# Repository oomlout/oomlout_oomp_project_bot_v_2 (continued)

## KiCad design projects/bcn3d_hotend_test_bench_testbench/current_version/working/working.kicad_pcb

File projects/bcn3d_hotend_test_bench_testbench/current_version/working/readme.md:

# hotend_test_bench
 
## summary 
* id: bcn3d_hotend_test_bench_testbench
* user: bcn3d
* name: hotend_test_bench
* board: testbench
* repo: https://github.com/BCN3D/Hotend-Test-Bench

* src_file_repo_sch: 
* src_file_repo_sch_link: https://github.com/BCN3D/Hotend-Test-Bench/tree/master/
* full details link: https://github.com/oomlout/oomlout_oomp_project_bot_v_2/tree/main/projects/bcn3d_hotend_test_bench_testbench/current_version/working  

## schematic  
  
[schematic (pdf)](working_schematic.pdf) 

## pcb  

[board (pdf)](working.pdf)  

## working_bom
| Id | Designator | Footprint | Quantity | Designation | Supplier and ref |  | None | 
| --- | --- | --- | --- | --- | --- | --- | --- | 
| 1 | R21,R13,R5,R17,R1,R9,R25 | R0805 | 7 | 5k6 |  |  | [''] | 
| 2 | C3,C12,C1,C13,C18,C15,C17,C11,C6,C19,C10,C9,C4,C16,C5,C2 | C0805K | 16 | 100n |  |  | [''] | 
| 3 | F1 | PTC-1206-WIDE | 1 | PTCSMD-W |  |  | [''] | 
| 4 | C7,C8 | C0805K | 2 | 22p |  |  | [''] | 
| 5 | R11,R15,R7,R23,R26,R3,R19 | R0805 | 7 | 10k |  |  | [''] | 
| 6 | R14,R18,R10,R2,R22,R6 | R0805 | 6 | 100 |  |  | [''] | 
| 7 | D5,D1,D7,D3,D4,D6,D2 | SMA-DIODE | 7 | MBRA140 |  |  | [''] | 
| 8 | R20,R8,R24,R12,R4,R16 | R0805 | 6 | 4k7 |  |  | [''] | 
| 9 | Q3,Q2,Q6,Q4,Q1,Q5 | SOIC8 | 6 | MOSFET-N |  |  | [''] | 
| 10 | C14 | C0805K | 1 | 330n |  |  | [''] | 
| 11 | LED3,LED1,LED5,LED4,LED6,LED2,LED16,LED13,LED14,LED18,+5V0,LED15,LED10,LED8,LED11,LED17,LED9,LED12,LED7,+24V0 | CHIP-LED0805 | 20 |  |  |  | [''] | 
| 12 | PC1 | MOLEX_MINIFIT-JR | 1 | POWER INPUT |  |  | [''] | 
| 13 | HOTEND5,HOTEND6,HOTEND1,HOTEND3,HOTEND2,HOTEND4 | 1X04 | 6 |  |  |  | [''] | 
| 14 | @HOLE0,@HOLE1 |  | 2 |  |  |  | [''] | 
| 15 | U1 | TQFP32-08 | 1 | ATMEGA328P_TQFP |  |  | [''] | 
| 16 | IC2,IC1 | SO16 | 2 | 74LS595D |  |  | [''] | 
| 17 | RESET0 | EVQ-Q2 | 1 | SPST_TACT-EVQQ2 |  |  | [''] | 
| 18 | U$3 | OSHW-LOGO-L | 1 |  |  |  | [''] | 
| 19 | ICSP0 | 2X3 | 1 | AVR_SPI_PRG_6PTH |  |  | [''] | 
| 20 | Y1 | HC49US | 1 | 16MHz |  |  | [''] | 
| 21 | U2 | TO-252 | 1 | KA7805ERTF |  |  | [''] | 
| 22 | JP8 | FTDI_BASIC | 1 | FTDI_BASICPTH |  |  | [''] | 
| 23 | RN2,RN3,RN1 | CTS742C083 | 3 | CTS742C083 |  |  | [''] | 
| 24 | R27 | R0805 | 1 | 1k |  |  | [''] | 
| 25 | U$2 | BCN3D_LOGO | 1 |  |  |  | [''] | 
| 26 | U$1 | FCIM_LOGO | 1 |  |  |  | [''] | 

## bom_schematic
| Ref | Qnty | Value | Cmp name | Footprint | Description | Vendor | DNP | 
| --- | --- | --- | --- | --- | --- | --- | --- | 
| +5V0 | 1 | LEDCHIP-LED0805 | LEDCHIP-LED0805 | working:CHIP-LED0805 |  |  |  | 
| +24V0 | 1 | LEDCHIP-LED0805 | LEDCHIP-LED0805 | working:CHIP-LED0805 |  |  |  | 
| C1, C2, C3, C4, C5, C6, C9, C10, C11, C12, C13, C15, C16, C17, C18, C19 | 16 | 100n | C-USC0805K | working:C0805K |  |  |  | 
| C7, C8 | 2 | 22p | C-USC0805K | working:C0805K |  |  |  | 
| C14 | 1 | 330n | C-USC0805K | working:C0805K |  |  |  | 
| D1, D2, D3, D4, D5, D6, D7 | 7 | MBRA140 | MBRA140 | working:SMA-DIODE |  |  |  | 
| F1 | 1 | PTCSMD-W | PTCSMD-W | working:PTC-1206-WIDE |  |  |  | 
| HOTEND1, HOTEND2, HOTEND3, HOTEND4, HOTEND5, HOTEND6 | 6 | PINHD-1X4 | PINHD-1X4 | working:1X04 |  |  |  | 
| IC1, IC2 | 2 | 74595D | 74595D | working:SO16 |  |  |  | 
| ICSP0 | 1 | AVR_SPI_PRG_6PTH | AVR_SPI_PRG_6PTH | working:2X3 |  |  |  | 
| JP8 | 1 | FTDI_BASICPTH | FTDI_BASICPTH | working:FTDI_BASIC |  |  |  | 
| LED1, LED2, LED3, LED4, LED5, LED6, LED7, LED8, LED9, LED10, LED11, LED12, LED13, LED14, LED15, LED16, LED17, LED18 | 18 | LEDCHIP-LED0805 | LEDCHIP-LED0805 | working:CHIP-LED0805 |  |  |  | 
| PC1 | 1 | POWER_CONNECTOR_4WAY | POWER_CONNECTOR_4WAY | working:MOLEX_MINIFIT-JR |  |  |  | 
| Q1, Q2, Q3, Q4, Q5, Q6 | 6 | MOSFET-N | MarcEagleParts_MOSFET-N | working:SOIC8 |  |  |  | 
| R1, R5, R9, R13, R17, R21, R25 | 7 | 5k6 | R-US_R0805 | working:R0805 |  |  |  | 
| R2, R6, R10, R14, R18, R22 | 6 | 100 | R-US_R0805 | working:R0805 |  |  |  | 
| R3, R7, R11, R15, R19, R23, R26 | 7 | 10k | R-US_R0805 | working:R0805 |  |  |  | 
| R4, R8, R12, R16, R20, R24 | 6 | 4k7 | R-US_R0805 | working:R0805 |  |  |  | 
| R27 | 1 | 1k | R-US_R0805 | working:R0805 |  |  |  | 
| RESET0 | 1 | SPST_TACT-EVQQ2 | SPST_TACT-EVQQ2 | working:EVQ-Q2 |  |  |  | 
| RN1, RN2, RN3 | 3 | CTS742C083 | CTS742C083 | working:CTS742C083 |  |  |  | 
| U1 | 1 | ATMEGA328P_TQFP | ATMEGA328P_TQFP | working:TQFP32-08 |  |  |  | 
| U2 | 1 | KA7805ERTF | V_REG_78XX7812 | working:TO-252 |  |  |  | 
| Y1 | 1 | 16MHz | CRYSTALHC49US | working:HC49US |  |  |  |

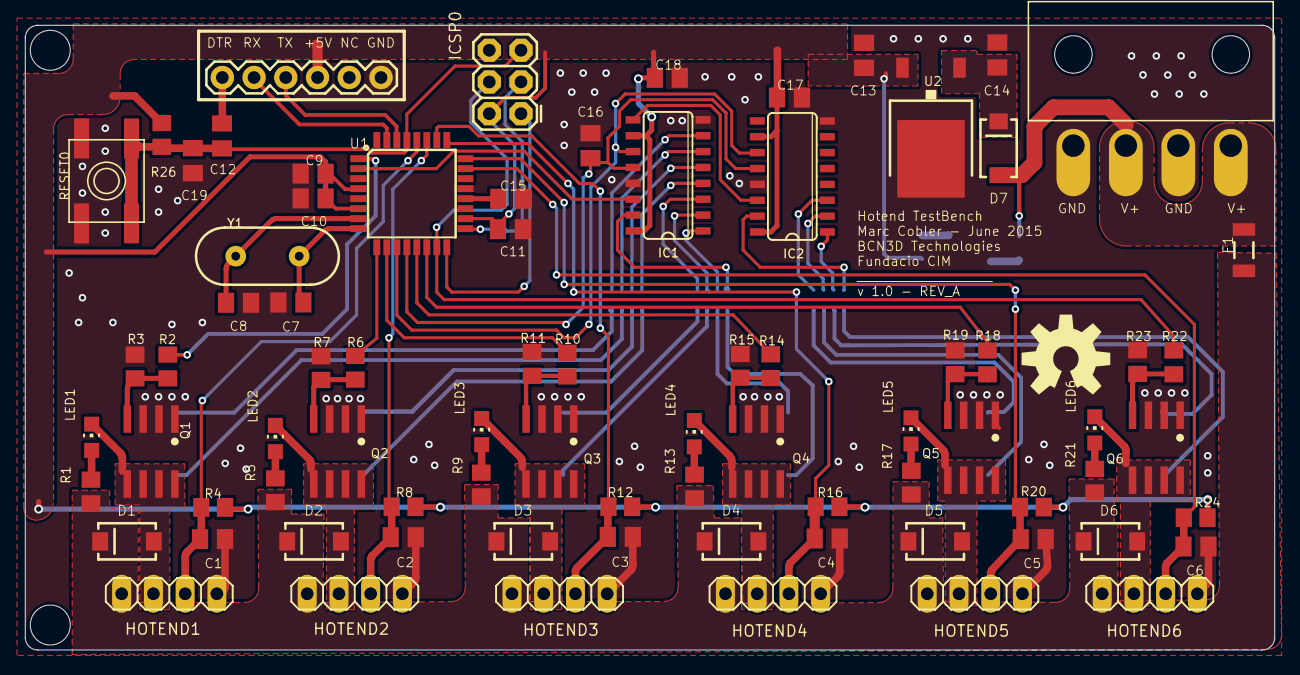
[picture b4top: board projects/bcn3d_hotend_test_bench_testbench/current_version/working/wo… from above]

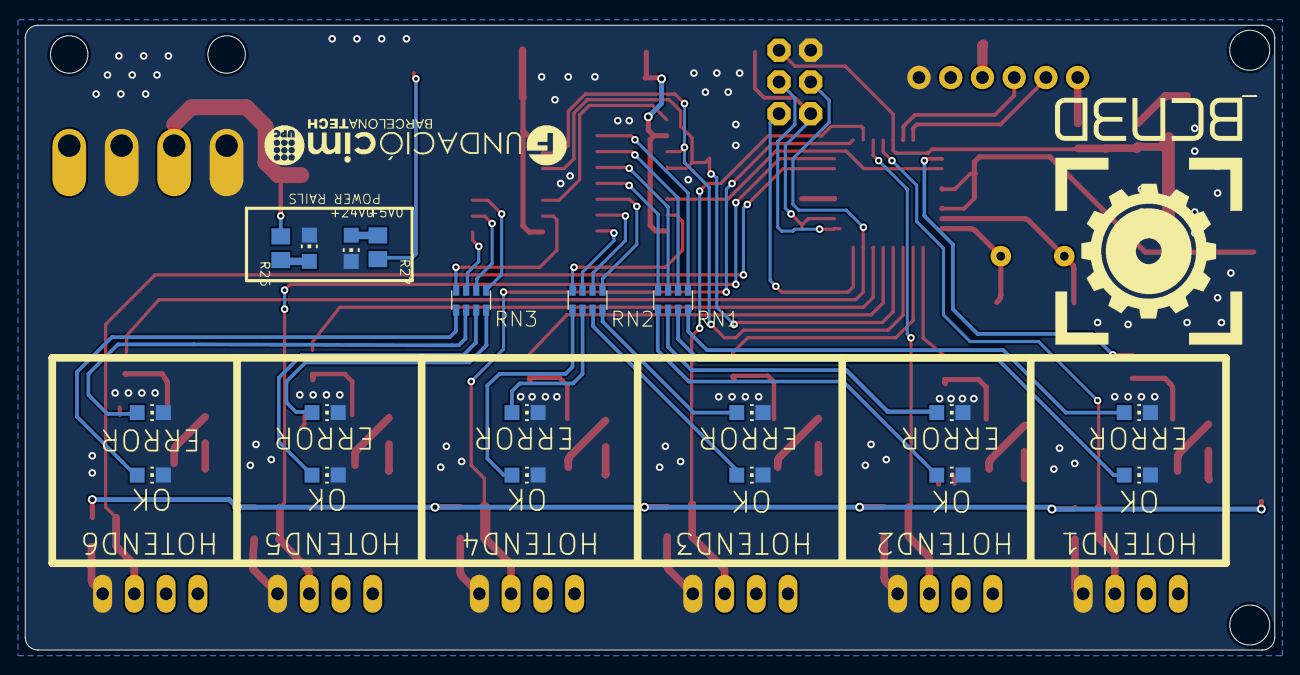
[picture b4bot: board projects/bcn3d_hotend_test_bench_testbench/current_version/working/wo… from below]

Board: 2 copper layers, 100.0 x 50.0 mm, 103 parts (21 on the bottom side), 74 nets.

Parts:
+5V0, +24V0: CHIP-LED0805
@HOLE0, @HOLE1: (no value)
C1, C2, C3, C4, C5, C6, C9, C10, C11, C12, C13, C15, C16, C17, C18, C19: 100n; C0805K
C7, C8: 22p; C0805K
C14: 330n; C0805K
D1, D2, D3, D4, D5, D6, D7: MBRA140; SMA-DIODE
F1: PTCSMD-W; PTC-1206-WIDE
HOTEND1, HOTEND2, HOTEND3, HOTEND4, HOTEND5, HOTEND6: 1X04
IC1, IC2: 74LS595D; SO16
ICSP0: AVR_SPI_PRG_6PTH; 2X3
JP8: FTDI_BASICPTH; FTDI_BASIC
LED1, LED2, LED3, LED4, LED5, LED6, LED7, LED8, LED9, LED10, LED11, LED12, LED13, LED14, LED15, LED16, LED17, LED18: CHIP-LED0805
PC1: POWER INPUT; MOLEX_MINIFIT-JR
Q1, Q2, Q3, Q4, Q5, Q6: MOSFET-N; SOIC8
R1, R5, R9, R13, R17, R21, R25: 5k6; R0805
R2, R6, R10, R14, R18, R22: 100; R0805
R3, R7, R11, R15, R19, R23, R26: 10k; R0805
R4, R8, R12, R16, R20, R24: 4k7; R0805
R27: 1k; R0805
RESET0: SPST_TACT-EVQQ2; EVQ-Q2
RN1, RN2, RN3: CTS742C083
U1: ATMEGA328P_TQFP; TQFP32-08
U2: KA7805ERTF; TO-252
U$1: FCIM_LOGO
U$2: BCN3D_LOGO
U$3: OSHW-LOGO-L
Y1: 16MHz; HC49US

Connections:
+5V: C9.1, C10.1, C11.1, C13.1, C17.1, C18.1, IC1.10, IC1.16, IC2.10, IC2.16, ICSP0.2, JP8.VCC, R4.1, R8.1, R12.1, R16.1, R20.1, R24.1, R26.1, R27.2, U1.4, U1.6, U1.18, U2.2
+24V: D7.A, F1.1, PC1.1, PC1.3, R25.2
+24VHE: D1.C, D2.C, D3.C, D4.C, D5.C, D6.C, F1.2, HOTEND1.1, HOTEND2.1, HOTEND3.1, HOTEND4.1, HOTEND5.1, HOTEND6.1, R1.2, R5.2, R9.2, R13.2, R17.2, R21.2
CLK: IC1.11, IC2.11, U1.11
DATA: IC1.14, U1.2
DTR: C12.2, JP8.DTR
GND: +5V0.C, +24V0.C, C1.2, C2.2, C3.2, C4.2, C5.2, C6.2, C7.2, C8.2, C9.2, C10.2, C11.2, C13.2, C14.2, C15.2, C16.2, C17.2, C18.2, C19.2, HOTEND1.4, HOTEND2.4, HOTEND3.4, HOTEND4.4, HOTEND5.4, HOTEND6.4, IC1.8, IC1.13, IC2.8, IC2.13, ICSP0.6, JP8.GND, LED7.C, LED8.C, LED9.C, LED10.C, LED11.C, LED12.C, LED13.C, LED14.C, LED15.C, LED16.C, LED17.C, LED18.C, PC1.2, PC1.4, Q1.1, Q1.2, Q1.3, Q2.1, Q2.2, Q2.3, Q3.1, Q3.2, Q3.3, Q4.1, Q4.2, Q4.3, Q5.1, Q5.2, Q5.3, Q6.1, Q6.2, Q6.3, R3.2, R7.2, R11.2, R15.2, R19.2, R23.2, RESET0.B, RESET0.B', U1.3, U1.5, U1.21, U2.3
H1: D1.A, HOTEND1.2, LED1.C, Q1.5, Q1.6, Q1.7, Q1.8
H2: D2.A, HOTEND2.2, LED2.C, Q2.5, Q2.6, Q2.7, Q2.8
H3: D3.A, HOTEND3.2, LED3.C, Q3.5, Q3.6, Q3.7, Q3.8
H4: D4.A, HOTEND4.2, LED4.C, Q4.5, Q4.6, Q4.7, Q4.8
H5: D5.A, HOTEND5.2, LED5.C, Q5.5, Q5.6, Q5.7, Q5.8
H6: D6.A, HOTEND6.2, LED6.C, Q6.5, Q6.6, Q6.7, Q6.8
LATCH: C16.1, IC1.12, IC2.12, U1.12
LED0: IC1.15, RN2.4
LED1: IC1.1, RN2.3
LED2: IC1.2, RN2.2
LED3: IC1.3, RN2.1
LED4: IC1.4, RN1.4
LED5: IC1.5, RN1.3
LED6: IC1.6, RN1.2
LED7: IC1.7, RN1.1
LED8: IC2.15, RN3.4
LED9: IC2.1, RN3.3
LED10: IC2.2, RN3.2
LED11: IC2.3, RN3.1
MISO: ICSP0.1, U1.16
unnamed: Q1.4, R2.1, R3.1
unnamed: +24V0.A, R25.1
unnamed: LED1.A, R1.1
unnamed: Q5.4, R18.1, R19.1
unnamed: C7.1, U1.8, Y1.1
unnamed: LED7.A, RN1.8
unnamed: Q2.4, R6.1, R7.1
unnamed: LED2.A, R5.1
unnamed: Q3.4, R10.1, R11.1
unnamed: LED3.A, R9.1
unnamed: Q4.4, R14.1, R15.1
unnamed: LED4.A, R13.1
unnamed: LED5.A, R17.1
unnamed: Q6.4, R22.1, R23.1
unnamed: LED6.A, R21.1
unnamed: C8.1, U1.7, Y1.2
unnamed: C15.1, U1.20
unnamed: C14.1, D7.C, U2.1
unnamed: LED8.A, RN1.7
unnamed: LED9.A, RN1.6
unnamed: LED10.A, RN1.5
unnamed: LED11.A, RN2.8
unnamed: LED12.A, RN2.7
unnamed: LED13.A, RN2.6
unnamed: LED14.A, RN2.5
unnamed: LED15.A, RN3.8
unnamed: LED16.A, RN3.7
unnamed: LED17.A, RN3.6
unnamed: LED18.A, RN3.5
unnamed: IC1.9, IC2.14
unnamed: +5V0.A, R27.1
PWM0: R2.2, U1.1
PWM1: R6.2, U1.9
PWM2: R10.2, U1.10
PWM3: R14.2, U1.13
PWM4: R18.2, U1.14
PWM5: ICSP0.4, R22.2, U1.15
RX: JP8.RXI, U1.31
SCK: ICSP0.3, U1.17
THERM0: C1.1, HOTEND1.3, R4.2, U1.28
THERM1: C2.1, HOTEND2.3, R8.2, U1.27
THERM2: C3.1, HOTEND3.3, R12.2, U1.26
THERM3: C4.1, HOTEND4.3, R16.2, U1.25
THERM4: C5.1, HOTEND5.3, R20.2, U1.24
THERM5: C6.1, HOTEND6.3, R24.2, U1.23
TX: JP8.TXO, U1.30
~RESET: C12.1, C19.1, ICSP0.5, R26.2, RESET0.A, RESET0.A', U1.29

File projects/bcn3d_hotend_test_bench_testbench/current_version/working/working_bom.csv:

"Id";"Designator";"Footprint";"Quantity";"Designation";"Supplier and ref";
1;"R21,R13,R5,R17,R1,R9,R25";"R0805";7;"5k6";;;
2;"C3,C12,C1,C13,C18,C15,C17,C11,C6,C19,C10,C9,C4,C16,C5,C2";"C0805K";16;"100n";;;
3;"F1";"PTC-1206-WIDE";1;"PTCSMD-W";;;
4;"C7,C8";"C0805K";2;"22p";;;
5;"R11,R15,R7,R23,R26,R3,R19";"R0805";7;"10k";;;
6;"R14,R18,R10,R2,R22,R6";"R0805";6;"100";;;
7;"D5,D1,D7,D3,D4,D6,D2";"SMA-DIODE";7;"MBRA140";;;
8;"R20,R8,R24,R12,R4,R16";"R0805";6;"4k7";;;
9;"Q3,Q2,Q6,Q4,Q1,Q5";"SOIC8";6;"MOSFET-N";;;
10;"C14";"C0805K";1;"330n";;;
11;"LED3,LED1,LED5,LED4,LED6,LED2,LED16,LED13,LED14,LED18,+5V0,LED15,LED10,LED8,LED11,LED17,LED9,LED12,LED7,+24V0";"CHIP-LED0805";20;"";;;
12;"PC1";"MOLEX_MINIFIT-JR";1;"POWER INPUT";;;
13;"HOTEND5,HOTEND6,HOTEND1,HOTEND3,HOTEND2,HOTEND4";"1X04";6;"";;;
14;"@HOLE0,@HOLE1";"";2;"";;;
15;"U1";"TQFP32-08";1;"ATMEGA328P_TQFP";;;
16;"IC2,IC1";"SO16";2;"74LS595D";;;
17;"RESET0";"EVQ-Q2";1;"SPST_TACT-EVQQ2";;;
18;"U$3";"OSHW-LOGO-L";1;"";;;
19;"ICSP0";"2X3";1;"AVR_SPI_PRG_6PTH";;;
20;"Y1";"HC49US";1;"16MHz";;;
21;"U2";"TO-252";1;"KA7805ERTF";;;
22;"JP8";"FTDI_BASIC";1;"FTDI_BASICPTH";;;
23;"RN2,RN3,RN1";"CTS742C083";3;"CTS742C083";;;
24;"R27";"R0805";1;"1k";;;
25;"U$2";"BCN3D_LOGO";1;"";;;
26;"U$1";"FCIM_LOGO";1;"";;;

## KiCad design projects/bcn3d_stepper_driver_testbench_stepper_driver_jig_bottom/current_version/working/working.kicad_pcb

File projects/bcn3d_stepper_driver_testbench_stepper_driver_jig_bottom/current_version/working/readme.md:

# stepper_driver_testbench
 
## summary 
* id: bcn3d_stepper_driver_testbench_stepper_driver_jig_bottom
* user: bcn3d
* name: stepper_driver_testbench
* board: stepper_driver_jig_bottom
* repo: https://github.com/BCN3D/Stepper-Driver-testbench

* src_file_repo_sch: 
* src_file_repo_sch_link: https://github.com/BCN3D/Stepper-Driver-testbench/tree/master/
* full details link: https://github.com/oomlout/oomlout_oomp_project_bot_v_2/tree/main/projects/bcn3d_stepper_driver_testbench_stepper_driver_jig_bottom/current_version/working  

## schematic  
  
[schematic (pdf)](working_schematic.pdf) 

## pcb  

[board (pdf)](working.pdf)  

## working_bom
| Id | Designator | Footprint | Quantity | Designation | Supplier and ref |  | None | 
| --- | --- | --- | --- | --- | --- | --- | --- | 
| 1 | R29,R30,R13,R12,R16,R1,R28,R4,R27,R18,R2,R14,R15,R3,R17,R11 | M0805 | 16 |  |  |  | [''] | 
| 2 | FTDI0 | FTDI_BASIC | 1 | FTDI_BASICPTH |  |  | [''] | 
| 3 | R7,R26,R8 | M0805 | 3 | 68.1K |  |  | [''] | 
| 4 | LED1 | CHIP-LED0805 | 1 |  |  |  | [''] | 
| 5 | @HOLE0,@HOLE1 |  | 2 |  |  |  | [''] | 
| 6 | U$11 | BCN3D_LOGO | 1 |  |  |  | [''] | 
| 7 | JP12,JP10,JP15,JP9,JP6,JP11,JP13,JP7,JP5,JP2,JP14,JP4,JP3,JP8 | POGOPIN | 14 |  |  |  | [''] | 
| 8 | U$3 | USB-B-PTH | 1 | USB+SHIELD |  |  | [''] | 
| 9 | JST0 | JST-PH-2-SMT-RA | 1 |  |  |  | [''] | 
| 10 | U$9,U$6,U$7,U$5,U$4,U$8 | STAND-OFF | 6 |  |  |  | [''] | 
| 11 | R20,R19 | M0805 | 2 | 10M |  |  | [''] | 
| 12 | RESET0 | EVQ-Q2 | 1 | SPST_TACT-EVQQ2 |  |  | [''] | 
| 13 | U$10 | FCIM_LOGO | 1 |  |  |  | [''] | 
| 14 | U$1,U$2 | CAPSENSE_PAD | 2 | CAPSENSE_PAD |  |  | [''] | 
| 15 | Q2 | SOT23-3 | 1 | MMBT2222A |  |  | [''] | 
| 16 | LOW0,HIGH0,OK0 | CHIPLED_1206 | 3 |  |  |  | [''] | 
| 17 | R10,R31,R5,R6 | M0805 | 4 | 1K |  |  | [''] | 
| 18 | R24,R25 | M0805 | 2 | 5.6K |  |  | [''] | 
| 19 | C5,C13,C9,C8,C6,C1,C7,C12 | C0805 | 8 | 100n |  |  | [''] | 
| 20 | LED4,LED5 | CHIPLED_0805 | 2 |  |  |  | [''] | 
| 21 | U1 | TO-252 | 1 | +5V |  |  | [''] | 
| 22 | C4 | UD-8X10_NICHICON | 1 | 100uF |  |  | [''] | 
| 23 | R22 | M0805 | 1 | 100 |  |  | [''] | 
| 24 | S2,S1 | SWITCH-SPDT_KIT | 2 |  |  |  | [''] | 
| 25 | SCREW0 | 1X01 | 1 |  |  |  | [''] | 
| 26 | R21,R23,R9 | M0805 | 3 | 10K |  |  | [''] | 
| 27 | IC2 | SO14 | 1 | LM339D |  |  | [''] | 
| 28 | Q3 | TO220V | 1 | MOSFET-PCHANNELFQP27P06 |  |  | [''] | 
| 29 | JP1 | POWER_JACK_PTH | 1 | POWER_JACKPTH |  |  | [''] | 
| 30 | MOTOR0 | 1X04 | 1 |  |  |  | [''] | 
| 31 | U3 | TQFP32-08 | 1 | ATMEGA328P |  |  | [''] | 
| 32 | C2 | C0805 | 1 | 1uF |  |  | [''] | 
| 33 | C10,C11 | C0805 | 2 | 22p |  |  | [''] | 
| 34 | Y1 | HC49US | 1 |  |  |  | [''] | 
| 35 | SH1 | SHORT_TOP-50 | 1 | SHORTT5 |  |  | [''] | 
| 36 | PORTC0 | 1X08 | 1 |  |  |  | [''] | 
| 37 | U2 | SO16 | 1 | 74HC4052 |  |  | [''] | 
| 38 | C3 | C0805 | 1 | 0.33uF |  |  | [''] | 
| 39 | ICSP0 | 2X3 | 1 | AVR_SPI_PRG_6PTH |  |  | [''] | 

## bom_schematic
| Ref | Qnty | Value | Cmp name | Footprint | Description | Vendor | DNP | 
| --- | --- | --- | --- | --- | --- | --- | --- | 
| C1, C5, C6, C7, C8, C9, C12, C13 | 8 | 100n | C-USC0805 | working:C0805 |  |  |  | 
| C2 | 1 | 1uF | C-USC0805 | working:C0805 |  |  |  | 
| C3 | 1 | 0.33uF | C-USC0805 | working:C0805 |  |  |  | 
| C4 | 1 | 100uF | CPOL-USUD-8X10 | working:UD-8X10_NICHICON |  |  |  | 
| C10, C11 | 2 | 22p | C-USC0805 | working:C0805 |  |  |  | 
| FTDI0 | 1 | FTDI_BASICPTH | FTDI_BASICPTH | working:FTDI_BASIC |  |  |  | 
| HIGH0 | 1 | LEDCHIPLED_1206 | LEDCHIPLED_1206 | working:CHIPLED_1206 |  |  |  | 
| IC2 | 1 | LM339D | LM339D | working:SO14 |  |  |  | 
| ICSP0 | 1 | AVR_SPI_PRG_6PTH | AVR_SPI_PRG_6PTH | working:2X3 |  |  |  | 
| JP1 | 1 | POWER_JACKPTH | POWER_JACKPTH | working:POWER_JACK_PTH |  |  |  | 
| JP2, JP3, JP4, JP5, JP6, JP7, JP8, JP9, JP10, JP11, JP12, JP13, JP14, JP15 | 14 | PINHD-1X1 | MarcEagleParts_PINHD-1X1 | working:POGOPIN |  |  |  | 
| JST0 | 1 | JST_2PIN-SMT-RA | JST_2PIN-SMT-RA | working:JST-PH-2-SMT-RA |  |  |  | 
| LED1 | 1 | LEDCHIP-LED0805 | LEDCHIP-LED0805 | working:CHIP-LED0805 |  |  |  | 
| LED4, LED5 | 2 | LEDCHIPLED_0805 | LEDCHIPLED_0805 | working:CHIPLED_0805 |  |  |  | 
| LOW0 | 1 | LEDCHIPLED_1206 | LEDCHIPLED_1206 | working:CHIPLED_1206 |  |  |  | 
| MOTOR0 | 1 | PINHD-1X4 | PINHD-1X4 | working:1X04 |  |  |  | 
| OK0 | 1 | LEDCHIPLED_1206 | LEDCHIPLED_1206 | working:CHIPLED_1206 |  |  |  | 
| PORTC0 | 1 | PINHD-1X8 | PINHD-1X8 | working:1X08 |  |  |  | 
| Q2 | 1 | MMBT2222A | TRANSISTOR_NPNMMBT2222A | working:SOT23-3 |  |  |  | 
| Q3 | 1 | MOSFET-PCHANNELFQP27P06 | MOSFET-PCHANNELFQP27P06 | working:TO220V |  |  |  | 
| R1, R2, R3, R4, R11, R12, R13, R14, R15, R16, R17, R18, R27, R28, R29, R30 | 16 | R-US_M0805 | R-US_M0805 | working:M0805 |  |  |  | 
| R5, R6, R10, R31 | 4 | 1K | R-US_M0805 | working:M0805 |  |  |  | 
| R7, R8, R26 | 3 | 68.1K | R-US_M0805 | working:M0805 |  |  |  | 
| R9, R21, R23 | 3 | 10K | R-US_M0805 | working:M0805 |  |  |  | 
| R19, R20 | 2 | 10M | R-US_M0805 | working:M0805 |  |  |  | 
| R22 | 1 | 100 | R-US_M0805 | working:M0805 |  |  |  | 
| R24, R25 | 2 | 5.6K | R-US_M0805 | working:M0805 |  |  |  | 
| RESET0 | 1 | SPST_TACT-EVQQ2 | SPST_TACT-EVQQ2 | working:EVQ-Q2 |  |  |  | 
| S1, S2 | 2 | SWITCH-SPDTKIT | SWITCH-SPDTKIT | working:SWITCH-SPDT_KIT |  |  |  | 
| SCREW0 | 1 | PINHD-1X1 | PINHD-1X1 | working:1X01 |  |  |  | 
| SH1 | 1 | SHORTT5 | SHORTT5 | working:SHORT_TOP-50 |  |  |  | 
| U1 | 1 | +5V | V_REG_78XX7812 | working:TO-252 |  |  |  | 
| U2 | 1 | 74HC4052SO | 74HC4052SO | working:SO16 |  |  |  | 
| U3 | 1 | ATMEGA328P_TQFP | ATMEGA328P_TQFP | working:TQFP32-08 |  |  |  | 
| U$1, U$2 | 2 | CAPSENSE_PAD | CAPSENSE_PAD | working:CAPSENSE_PAD |  |  |  | 
| U$3 | 1 | USB+SHIELD | USB+SHIELD | working:USB-B-PTH |  |  |  | 
| Y1 | 1 | CRYSTALHC49US | CRYSTALHC49US | working:HC49US |  |  |  |

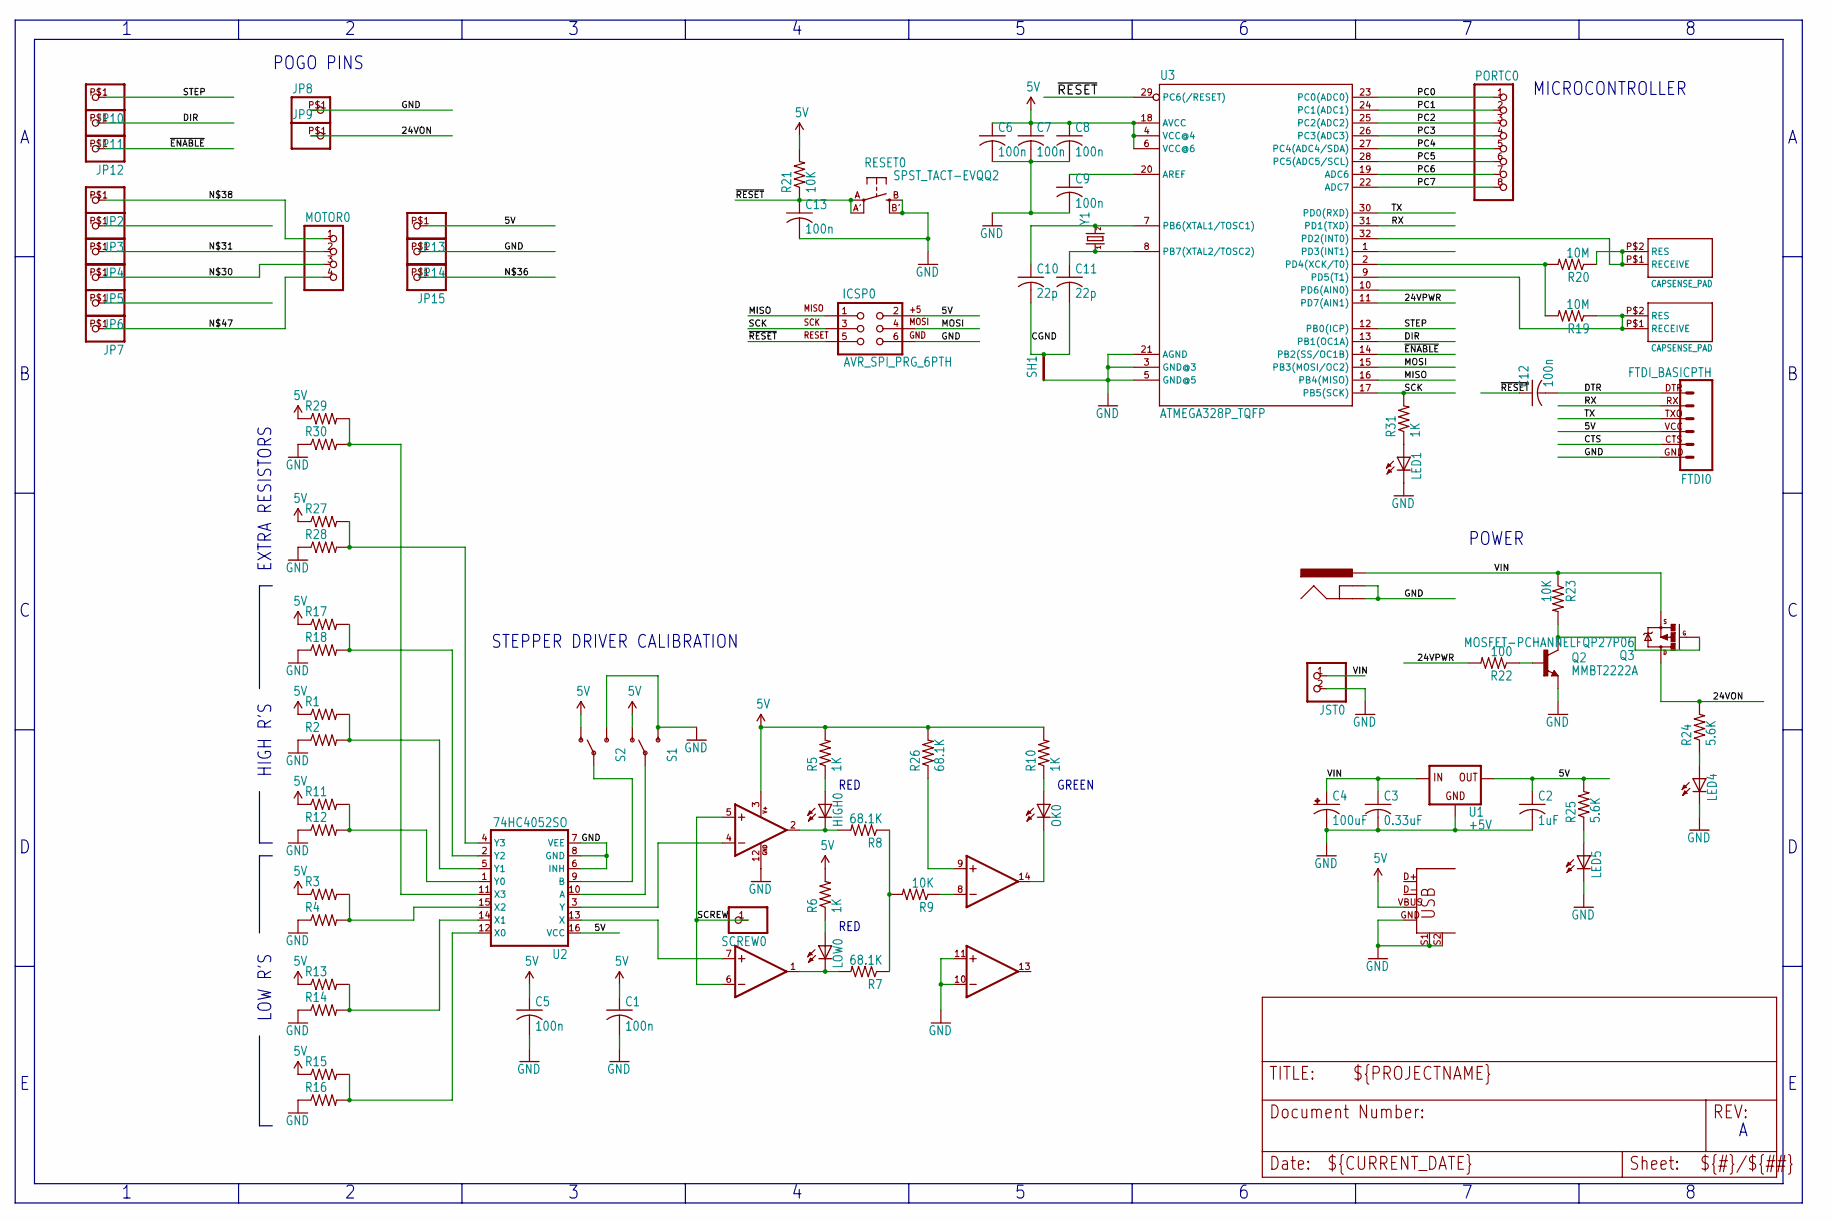
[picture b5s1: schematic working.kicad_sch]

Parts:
C1, C5, C6, C7, C8, C9, C12, C13: 100n; C0805
C2: 1uF; C0805
C3: 0.33uF; C0805
C4: 100uF; UD-8X10_NICHICON
C10, C11: 22p; C0805
FTDI0: FTDI_BASICPTH; FTDI_BASIC
HIGH0: LEDCHIPLED_1206; CHIPLED_1206
IC2: LM339D; SO14
ICSP0: AVR_SPI_PRG_6PTH; 2X3
JP1: POWER_JACKPTH; POWER_JACK_PTH
JP2, JP3, JP4, JP5, JP6, JP7, JP8, JP9, JP10, JP11, JP12, JP13, JP14, JP15: PINHD-1X1; POGOPIN
JST0: JST_2PIN-SMT-RA; JST-PH-2-SMT-RA
LED1: LEDCHIP-LED0805; CHIP-LED0805
LED4, LED5: LEDCHIPLED_0805; CHIPLED_0805
LOW0: LEDCHIPLED_1206; CHIPLED_1206
MOTOR0: PINHD-1X4; 1X04
OK0: LEDCHIPLED_1206; CHIPLED_1206
PORTC0: PINHD-1X8; 1X08
Q2: MMBT2222A; SOT23-3
Q3: MOSFET-PCHANNELFQP27P06; TO220V
R1, R2, R3, R4, R11, R12, R13, R14, R15, R16, R17, R18, R27, R28, R29, R30: R-US_M0805; M0805
R5, R6, R10, R31: 1K; M0805
R7, R8, R26: 68.1K; M0805
R9, R21, R23: 10K; M0805
R19, R20: 10M; M0805
R22: 100; M0805
R24, R25: 5.6K; M0805
RESET0: SPST_TACT-EVQQ2; EVQ-Q2
S1, S2: SWITCH-SPDTKIT; SWITCH-SPDT_KIT
SCREW0: PINHD-1X1; 1X01
SH1: SHORTT5; SHORT_TOP-50
U1: +5V; TO-252
U2: 74HC4052SO; SO16
U3: ATMEGA328P_TQFP; TQFP32-08
U$1, U$2: CAPSENSE_PAD
U$3: USB+SHIELD; USB-B-PTH
Y1: CRYSTALHC49US; HC49US

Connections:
5V: C1.1, C2.1, C5.1, C6.1, C7.1, C8.1, FTDI0.VCC (4), IC2.3 (V+), ICSP0.2, JP13.P$1, R1.1, R3.1, R5.2, R6.2, R10.2, R11.1, R13.1, R15.1, R17.1, R21.2, R25.2, R26.2, R27.1, R29.1, S1.1 (O), S2.1 (O), U1.2 (OUT), U2.16 (VCC), U3.4 (VCC@4), U3.6 (VCC@6), U3.18 (AVCC), U$3.VBUS
24VON: JP9.P$1, Q3.2 (D), R24.2
24VPWR: R22.2, U3.11 (PD7(AIN1))
CGND: C10.2, C11.2, SH1.2
CTS: FTDI0.CTS (5)
DIR: JP11.P$1, U3.13 (PB1(OC1A))
DTR: C12.2, FTDI0.DTR (1)
GND: C1.2, C2.2, C3.2, C4.-, C5.2, C6.2, C7.2, C8.2, C9.2, C13.2, FTDI0.GND (6), IC2.10 (-IN), IC2.11 (+IN), IC2.12 (GND), ICSP0.6, JP1.GND, JP1.GNDBREAK, JP8.P$1, JP14.P$1, JST0.2 (1), LED1.C, LED4.C, LED5.C, Q2.2 (E), R2.1, R4.1, R12.1, R14.1, R16.1, R18.1, R28.1, R30.1, RESET0.B (S), RESET0.B' (S1), S1.3 (S), S2.3 (S), SH1.1, U1.3 (GND), U2.6 (INH), U2.7 (VEE), U2.8 (GND), U3.3 (GND@3), U3.5 (GND@5), U3.21 (AGND), U$3.GND, U$3.S1, U$3.S2
MISO: ICSP0.1, U3.16 (PB4(MISO))
MOSI: ICSP0.4, U3.15 (PB3(MOSI/OC2))
unnamed: IC2.4 (-IN), U2.3 (Y)
unnamed: IC2.7 (+IN), U2.13 (X)
unnamed: IC2.1 (OUT), LOW0.C, R7.2
unnamed: LOW0.A, R6.1
unnamed: HIGH0.C, IC2.2 (OUT), R8.2
unnamed: HIGH0.A, R5.1
unnamed: R7.1, R8.1, R9.2
unnamed: IC2.8 (-IN), R9.1
unnamed: OK0.A, R10.1
unnamed: IC2.14 (OUT), OK0.C
unnamed: R11.2, R12.2, U2.1 (Y0)
unnamed: R1.2, R2.2, U2.5 (Y1)
unnamed: R3.2, R4.2, U2.15 (X2)
unnamed: R13.2, R14.2, U2.14 (X1)
unnamed: R15.2, R16.2, U2.12 (X0)
unnamed: R17.2, R18.2, U2.2 (Y2)
unnamed: S1.2, U2.10 (A)
unnamed: S2.2, U2.9 (B)
unnamed: R19.1, U3.9 (PD5(T1)), U$2.P$1 (RECEIVE), U$2.P$2 (RES)
unnamed: C11.1, U3.8 (PB7(XTAL2/TOSC2)), Y1.1
unnamed: C9.1, U3.20 (AREF)
unnamed: C10.1, U3.7 (PB6(XTAL1/TOSC1)), Y1.2
unnamed: Q2.3 (C), Q3.1 (G), R23.2
unnamed: Q2.1 (B), R22.1
unnamed: R19.2, R20.2, U3.2 (PD4(XCK/T0))
unnamed: R20.1, U3.32 (PD2(INT0)), U$1.P$1 (RECEIVE), U$1.P$2 (RES)
unnamed: JP5.P$1, MOTOR0.3
unnamed: JP4.P$1, MOTOR0.2
unnamed: JP2.P$1, MOTOR0.1
unnamed: LED4.A, R24.1
unnamed: LED5.A, R25.1
unnamed: JP7.P$1, MOTOR0.4
unnamed: IC2.9 (+IN), R26.1
unnamed: R27.2, R28.2, U2.4 (Y3)
unnamed: R29.2, R30.2, U2.11 (X3)
unnamed: LED1.A, R31.1
PC0: PORTC0.1, U3.23 (PC0(ADC0))
PC1: PORTC0.2, U3.24 (PC1(ADC1))
PC2: PORTC0.3, U3.25 (PC2(ADC2))
PC3: PORTC0.4, U3.26 (PC3(ADC3))
PC4: PORTC0.5, U3.27 (PC4(ADC4/SDA))
PC5: PORTC0.6, U3.28 (PC5(ADC5/SCL))
PC6: PORTC0.7, U3.19 (ADC6)
PC7: PORTC0.8, U3.22 (ADC7)
RX: FTDI0.RXI (2), U3.31 (PD1(TXD))
SCK: ICSP0.3, R31.2, U3.17 (PB5(SCK))
SCREW: IC2.5 (+IN), IC2.6 (-IN), SCREW0.1
STEP: JP10.P$1, U3.12 (PB0(ICP))
TX: FTDI0.TXO (3), U3.30 (PD0(RXD))
VIN: C3.1, C4.+, JP1.PWR, JST0.1 (2), Q3.3 (S), R23.1, U1.1 (IN)
~ENABLE: JP12.P$1, U3.14 (PB2(SS/OC1B))
~RESET: C12.1, C13.1, ICSP0.5, R21.1, RESET0.A, RESET0.A' (P1), U3.29 (PC6(/RESET))

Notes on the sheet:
POWER
LOW R'S
STEPPER DRIVER CALIBRATION
POGO PINS
RED
MICROCONTROLLER
GREEN
HIGH R'S
EXTRA RESISTORS

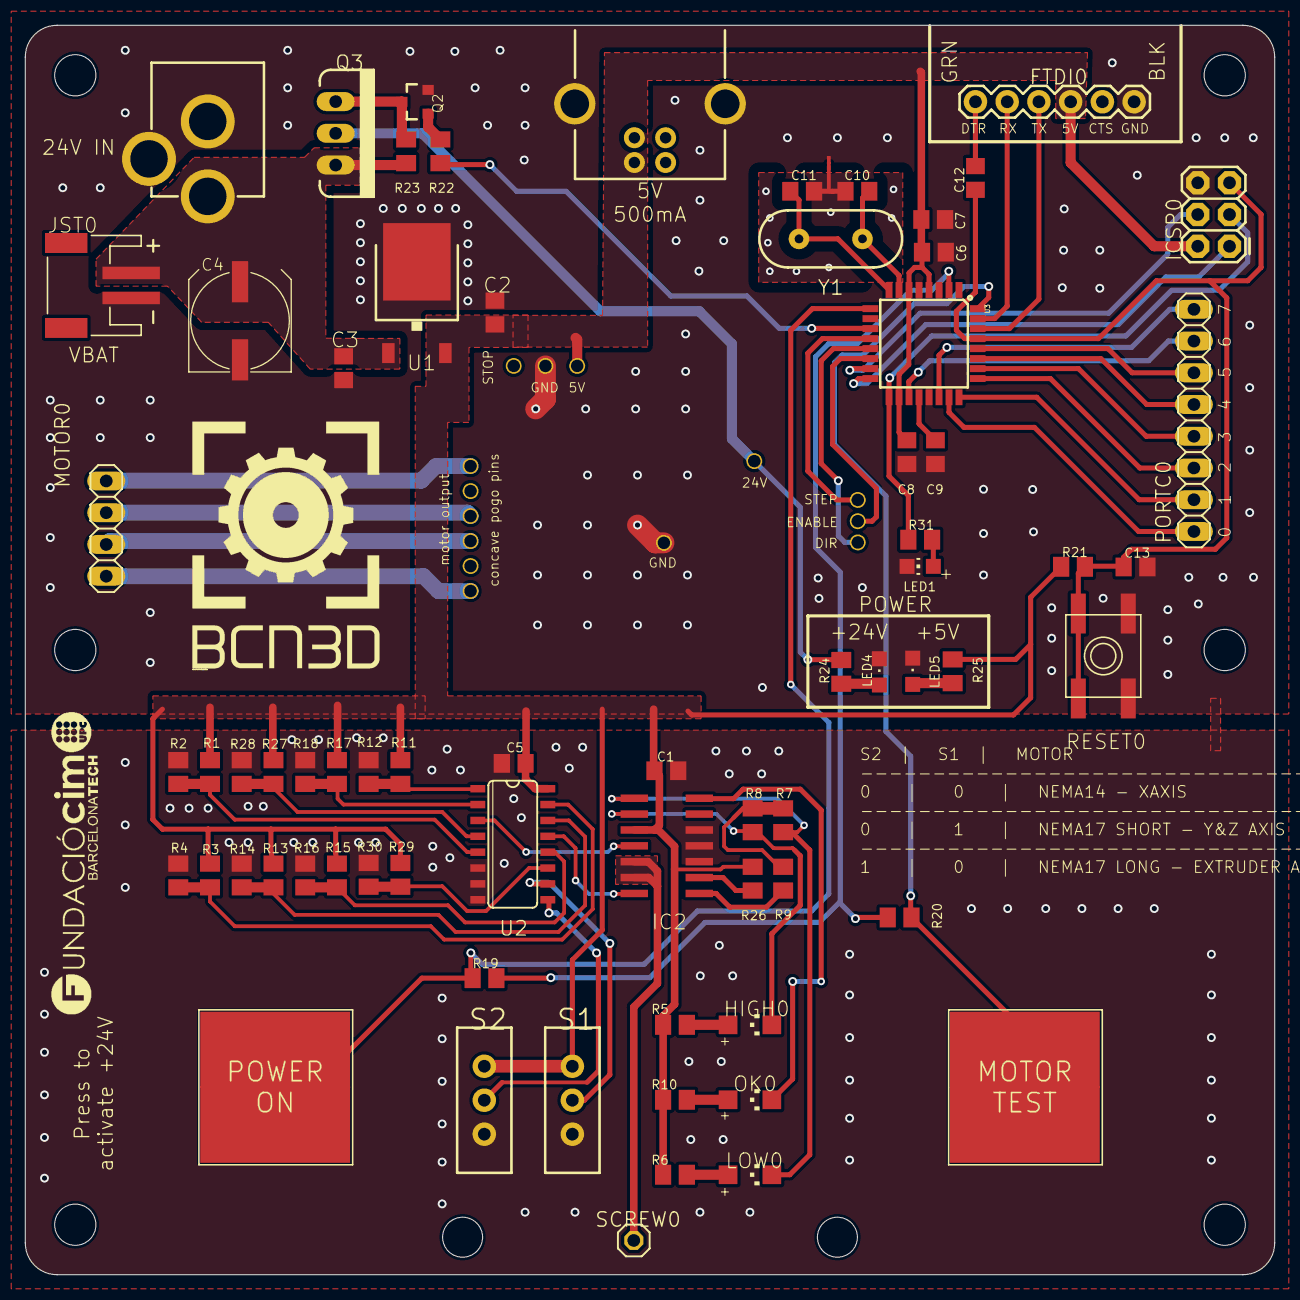
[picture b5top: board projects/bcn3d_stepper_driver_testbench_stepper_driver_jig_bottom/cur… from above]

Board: 2 copper layers, 100.0 x 100.0 mm, 95 parts (0 on the bottom side), 61 nets.

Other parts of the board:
@HOLE0, @HOLE1: (no value)
U$4, U$5, U$6, U$7, U$8, U$9: STAND-OFF
U$10: FCIM_LOGO
U$11: BCN3D_LOGO

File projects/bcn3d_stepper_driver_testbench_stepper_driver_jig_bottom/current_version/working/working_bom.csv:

"Id";"Designator";"Footprint";"Quantity";"Designation";"Supplier and ref";
1;"R29,R30,R13,R12,R16,R1,R28,R4,R27,R18,R2,R14,R15,R3,R17,R11";"M0805";16;"";;;
2;"FTDI0";"FTDI_BASIC";1;"FTDI_BASICPTH";;;
3;"R7,R26,R8";"M0805";3;"68.1K";;;
4;"LED1";"CHIP-LED0805";1;"";;;
5;"@HOLE0,@HOLE1";"";2;"";;;
6;"U$11";"BCN3D_LOGO";1;"";;;
7;"JP12,JP10,JP15,JP9,JP6,JP11,JP13,JP7,JP5,JP2,JP14,JP4,JP3,JP8";"POGOPIN";14;"";;;
8;"U$3";"USB-B-PTH";1;"USB+SHIELD";;;
9;"JST0";"JST-PH-2-SMT-RA";1;"";;;
10;"U$9,U$6,U$7,U$5,U$4,U$8";"STAND-OFF";6;"";;;
11;"R20,R19";"M0805";2;"10M";;;
12;"RESET0";"EVQ-Q2";1;"SPST_TACT-EVQQ2";;;
13;"U$10";"FCIM_LOGO";1;"";;;
14;"U$1,U$2";"CAPSENSE_PAD";2;"CAPSENSE_PAD";;;
15;"Q2";"SOT23-3";1;"MMBT2222A";;;
16;"LOW0,HIGH0,OK0";"CHIPLED_1206";3;"";;;
17;"R10,R31,R5,R6";"M0805";4;"1K";;;
18;"R24,R25";"M0805";2;"5.6K";;;
19;"C5,C13,C9,C8,C6,C1,C7,C12";"C0805";8;"100n";;;
20;"LED4,LED5";"CHIPLED_0805";2;"";;;
21;"U1";"TO-252";1;"+5V";;;
22;"C4";"UD-8X10_NICHICON";1;"100uF";;;
23;"R22";"M0805";1;"100";;;
24;"S2,S1";"SWITCH-SPDT_KIT";2;"";;;
25;"SCREW0";"1X01";1;"";;;
26;"R21,R23,R9";"M0805";3;"10K";;;
27;"IC2";"SO14";1;"LM339D";;;
28;"Q3";"TO220V";1;"MOSFET-PCHANNELFQP27P06";;;
29;"JP1";"POWER_JACK_PTH";1;"POWER_JACKPTH";;;
30;"MOTOR0";"1X04";1;"";;;
31;"U3";"TQFP32-08";1;"ATMEGA328P";;;
32;"C2";"C0805";1;"1uF";;;
33;"C10,C11";"C0805";2;"22p";;;
34;"Y1";"HC49US";1;"";;;
35;"SH1";"SHORT_TOP-50";1;"SHORTT5";;;
36;"PORTC0";"1X08";1;"";;;
37;"U2";"SO16";1;"74HC4052";;;
38;"C3";"C0805";1;"0.33uF";;;
39;"ICSP0";"2X3";1;"AVR_SPI_PRG_6PTH";;;

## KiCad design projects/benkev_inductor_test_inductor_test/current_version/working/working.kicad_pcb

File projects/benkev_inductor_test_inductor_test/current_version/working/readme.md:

# inductor_test
 
## summary 
* id: benkev_inductor_test_inductor_test
* user: benkev
* name: inductor_test
* board: inductor_test
* repo: https://github.com/benkev/inductor_test
* src_file_repo_kicad_pcb: inductor_test.kicad_pcb
* src_file_repo_kicad_pcb_link: https://github.com/benkev/inductor_test/tree/master/inductor_test.kicad_pcb

* src_file_repo_sch: inductor_test.sch
* src_file_repo_sch_link: https://github.com/benkev/inductor_test/tree/master/inductor_test.sch
* full details link: https://github.com/oomlout/oomlout_oomp_project_bot_v_2/tree/main/projects/benkev_inductor_test_inductor_test/current_version/working

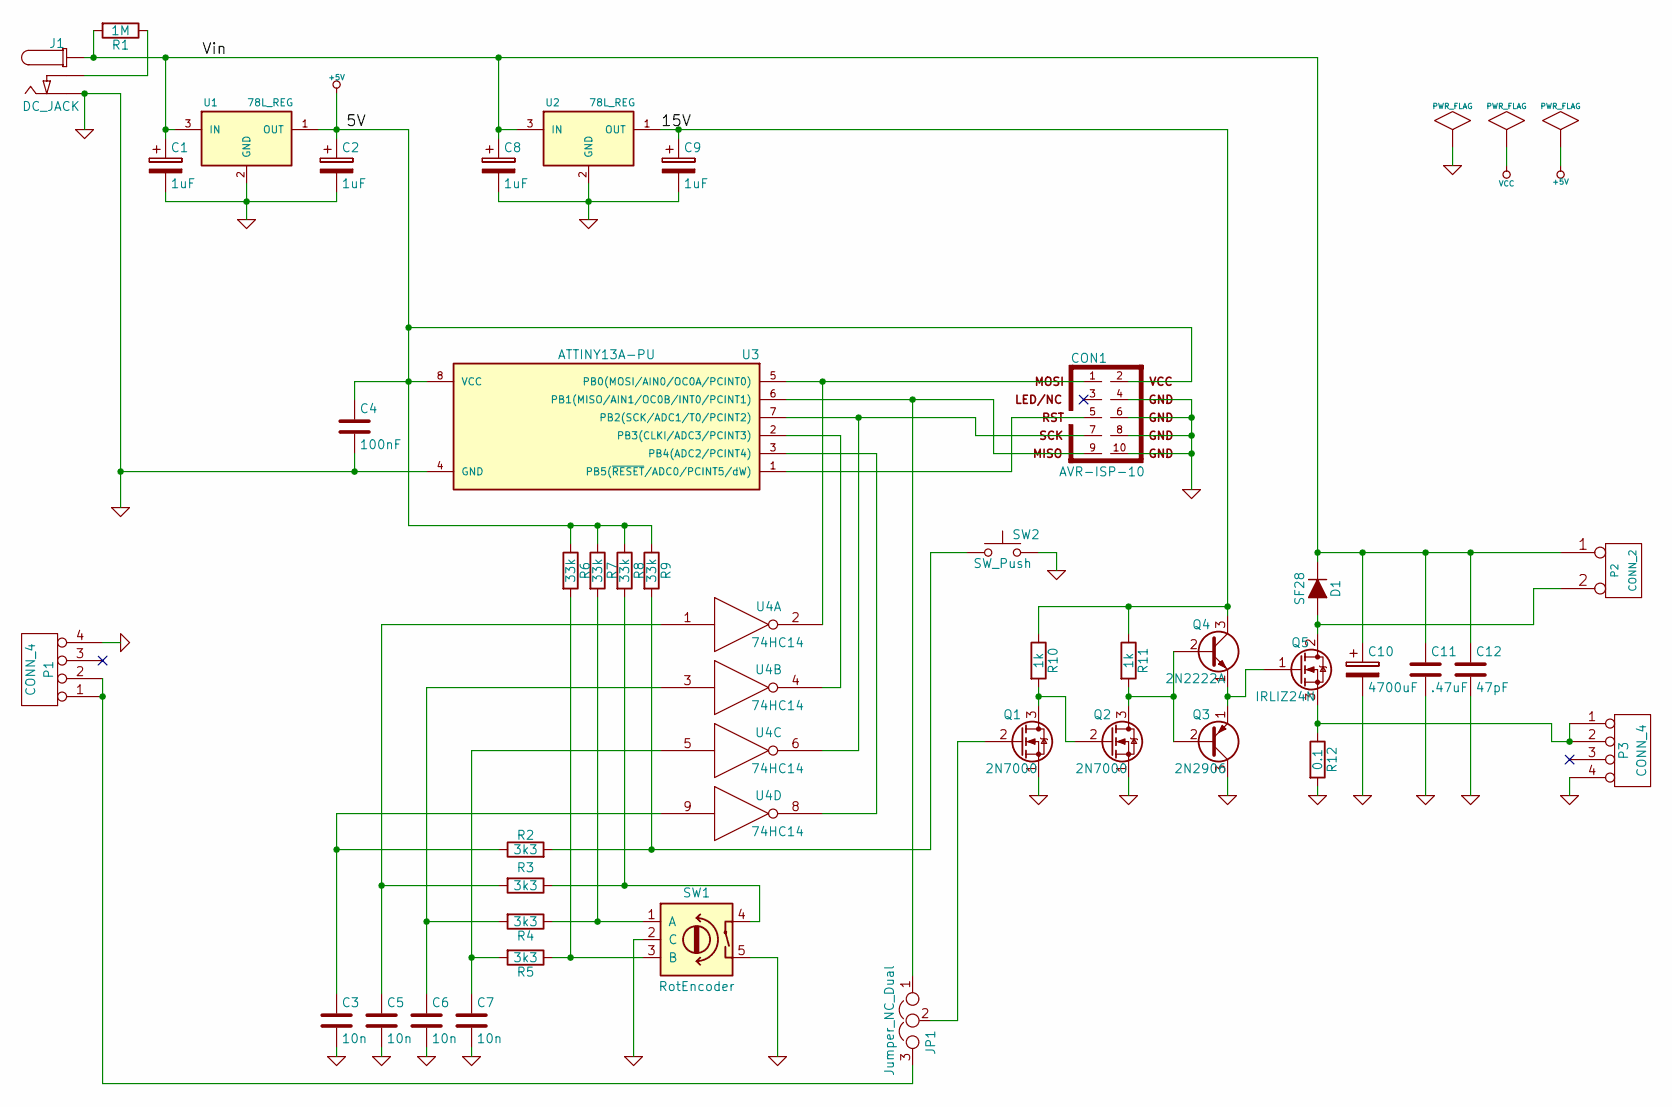
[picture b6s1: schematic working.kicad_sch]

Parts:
C1, C2, C8, C9: 1uF; C_0805
C3, C5, C6, C7: 10n; C_0805
C4: 100nF; C_0805
C10: 4700uF; CP_Radial_D16.0mm_P7.50mm
C11: .47uF; C_0805
C12: 47pF; C_0805
CON1: AVR-ISP-10; IDC_Header_Straight_10pins
D1: SF28; D_DO-27_P5.08mm_Vertical_AnodeUp
J1: DC_JACK; BARREL_JACK
JP1: Jumper_NC_Dual; Pin_Header_Angled_1x03_Pitch2.54mm
P1, P3: CONN_4; Pin_Header_Angled_1x04_Pitch2.54mm
P2: CONN_2; AK300-2
Q1, Q2: 2N7000; TO-92_Inline_Wide
Q3: 2N2906; TO-92_Inline_Wide
Q4: 2N2222A; TO-92_Inline_Wide
Q5: IRLIZ24N; TO-220-3
R1: 1M; R_0805
R2, R3, R4, R5: 3k3; R_0805
R6, R7, R8, R9: 33k; R_0805
R10, R11: 1k; R_0805
R12: 0.1; SolderWirePad_2x_1-5mmDrill
SW1: RotEncoder; PEC11_Switch_Rotary_Encoder
SW2: SW_Push; SW_PUSH_6mm
U1, U2: 78L_REG; TO-92_Inline_Wide
U3: ATTINY13A-PU; DIP-8_W7.62mm
U4: 74HC14; DIP-14_W7.62mm_Socket

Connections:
+5V: C2.1, C4.1, CON1.2, R6.1, R7.1, R8.1, R9.1, U1.1 (OUT), U3.8 (VCC)
/15V: C9.1, Q4.3 (C), R10.1, R11.1, U2.1 (OUT)
/Vin: C1.1, C8.1, C10.1, C11.1, C12.1, D1.1 (K), J1.1, P2.1, R1.2, U1.3 (IN), U2.3 (IN)
GND: C1.2, C2.2, C3.2, C4.2, C5.2, C6.2, C7.2, C8.2, C9.2, C10.2, C11.2, C12.2, CON1.4, CON1.6, CON1.8, CON1.10, J1.3 (P2), P1.4, P3.4, Q1.1 (S), Q2.1 (S), Q3.3 (C), R12.2, SW1.2 (C), SW1.5, SW2.2, U1.2 (GND), U2.2 (GND), U3.4 (GND), U4.7 (GND)
unnamed: C3.1, R2.1, U4.9
unnamed: C5.1, R3.2, U4.1
unnamed: C6.1, R4.2, U4.3
unnamed: C7.1, R5.2, U4.5
unnamed: CON1.1, U3.5 (PB0(MOSI/AIN0/OC0A/PCINT0)), U4.2
unnamed: CON1.5, U3.1 (PB5(~RESET/ADC0/PCINT5/dW))
unnamed: CON1.7, U3.7 (PB2(SCK/ADC1/T0/PCINT2)), U4.6
unnamed: CON1.9, JP1.1, U3.6 (PB1(MISO/AIN1/OC0B/INT0/PCINT1))
unnamed: D1.2 (A), P2.2 (PM), Q5.2 (D)
unnamed: J1.2 (P3), R1.1
unnamed: JP1.2, Q1.2 (G)
unnamed: JP1.3, P1.1, P1.2
unnamed: P3.1, P3.2, Q5.3 (S), R12.1
unnamed: Q1.3 (D), Q2.2 (G), R10.2
unnamed: Q2.3 (D), Q3.2 (B), Q4.2 (B), R11.2
unnamed: Q3.1 (E), Q4.1 (E), Q5.1 (G)
unnamed: R2.2, R9.2, SW2.1
unnamed: R3.1, R8.2, SW1.4
unnamed: R4.1, R7.2, SW1.1 (A)
unnamed: R5.1, R6.2, SW1.3 (B)
unnamed: U3.2 (PB3(CLKI/ADC3/PCINT3)), U4.4
unnamed: U3.3 (PB4(ADC2/PCINT4)), U4.8
VCC: U4.14 (VCC)

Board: 2 copper layers, 42 parts (0 on the bottom side), 26 nets, no tracks yet.
